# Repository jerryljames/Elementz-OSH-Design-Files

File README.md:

# Elementz Engineers Guild Pvt. Ltd. 

## Elementz-OSH-Design-Files
Open Source Hardware Design Files by Elementz

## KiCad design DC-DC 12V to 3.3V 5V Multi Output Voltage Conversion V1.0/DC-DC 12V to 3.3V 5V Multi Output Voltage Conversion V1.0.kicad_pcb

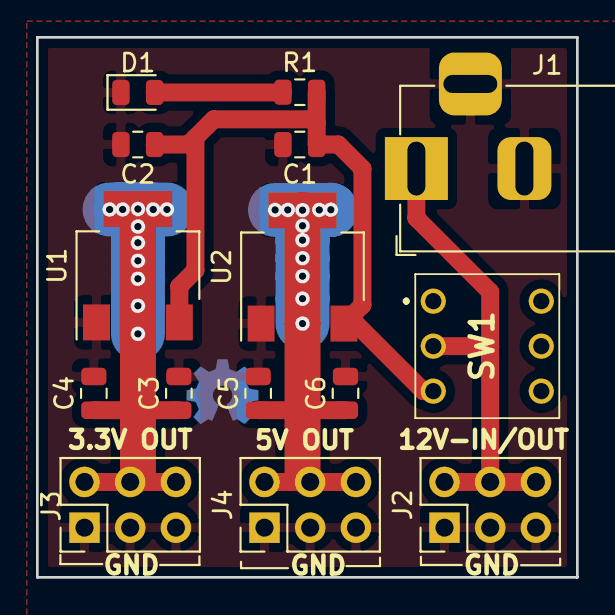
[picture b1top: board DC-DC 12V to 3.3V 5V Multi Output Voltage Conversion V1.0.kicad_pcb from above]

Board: 2 copper layers, 30.0 x 30.0 mm, 15 parts (0 on the bottom side), 6 nets.

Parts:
C1, C2, C3, C4, C5, C6: C; C_0805_2012Metric
D1: LED; LED_0805_2012Metric
J1: Barrel_Jack_Switch; BarrelJack_Horizontal
J2, J3, J4: Conn_02x03_Counter_Clockwise; PinHeader_2x03_P2.54mm_Vertical
R1: R; R_0805_2012Metric
SW1: SW_Push_DPDT; TL2285OA
U1: AMS1117-3.3; SOT-223-3_TabPin2
U2: AMS1117-5.0; SOT-223-3_TabPin2

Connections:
+3V3: C3.1, C4.1, J3.2, J3.4, J3.6, U1.2
+5V: C5.1, C6.1, J4.2, J4.4, J4.6, U2.2
+12V: J1.1, J2.2, J2.4, J2.6, SW1.2
GND: C1.2, C2.2, C3.2, C4.2, C5.2, C6.2, D1.1, J1.2, J1.3, J2.1, J2.3, J2.5, J3.1, J3.3, J3.5, J4.1, J4.3, J4.5, U1.1, U2.1
unnamed: D1.2, R1.1
VCC: C1.1, C2.1, R1.2, SW1.3, U1.3, U2.3

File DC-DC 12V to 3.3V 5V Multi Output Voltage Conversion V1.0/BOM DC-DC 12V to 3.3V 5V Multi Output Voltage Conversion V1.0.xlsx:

Comment | Designator | Footprint
10uF Unpolarized capacitor | C1,C2,C3,C5 | C_0805_2012Metric
0.1uF Unpolarized capacitor | C4,C6 | C_0805_2012Metric
LED Light emitting diode | D1 | LED_0805_2012Metric
Barrel_Jack_Switch DC Barrel Jack with an internal switch | J1 | BarrelJack_Horizontal
Conn_02x03_Counter_Clockwise | J2,J3,J4 | PinHeader_2x03_P2.54mm_Vertical
1K Resistor | R1 | R_0805_2012Metric
SW_Push_DPDT | SW1 | TL2285OA
AMS1117-3.3 1A Low Dropout regulator, positive, 3.3V fixed output, SOT-223 | U1 | SOT-223-3_TabPin2
AMS1117-5.0 1A Low Dropout regulator, positive, 5.0V fixed output, SOT-223 | U2 | SOT-223-3_TabPin2

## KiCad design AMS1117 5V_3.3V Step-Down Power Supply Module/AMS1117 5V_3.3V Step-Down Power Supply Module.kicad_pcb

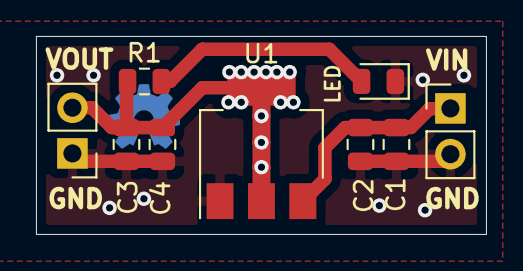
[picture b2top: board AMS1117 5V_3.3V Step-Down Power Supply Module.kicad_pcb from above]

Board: 2 copper layers, 25.0 x 11.0 mm, 9 parts (0 on the bottom side), 4 nets.

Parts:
C1, C2, C3, C4: C; C_0805_2012Metric
D1: LED; LED_0805_2012Metric
J1: Conn_01x02_Male; PinHeader_1x02_P2.54mm_Vertical
Je: Conn_01x02_Male; PinHeader_1x02_P2.54mm_Vertical
R1: R; R_0805_2012Metric
U1: AMS1117-3.3; SOT-223-3_TabPin2

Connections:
GND: C1.2, C2.2, C3.2, C4.2, D1.1, J1.2, Je.1, U1.1
unnamed: C1.1, C2.1, J1.1, U1.3
unnamed: C3.1, C4.1, Je.2, R1.2, U1.2
unnamed: D1.2, R1.1

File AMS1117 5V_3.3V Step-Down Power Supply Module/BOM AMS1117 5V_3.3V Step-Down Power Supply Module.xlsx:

Comment | Designator | Footprint
10uF Unpolarized capacitor | C1,C3 | C_0805_2012Metric
0.1uF Unpolarized capacitor | C2,C4 | C_0805_2012Metric
LED Light emitting diode | D1 | LED_0805_2012Metric
DNP (Do Not Populate) | J1,J2 | PinHeader_1x02_P2.54mm_Vertical
1K Resistor | R1 | R_0805_2012Metric
AMS1117 1A Low Dropout regulator, positive, fixed output, SOT-223 – 5V or 3.3V 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 | U1 | SOT-223-3_TabPin2

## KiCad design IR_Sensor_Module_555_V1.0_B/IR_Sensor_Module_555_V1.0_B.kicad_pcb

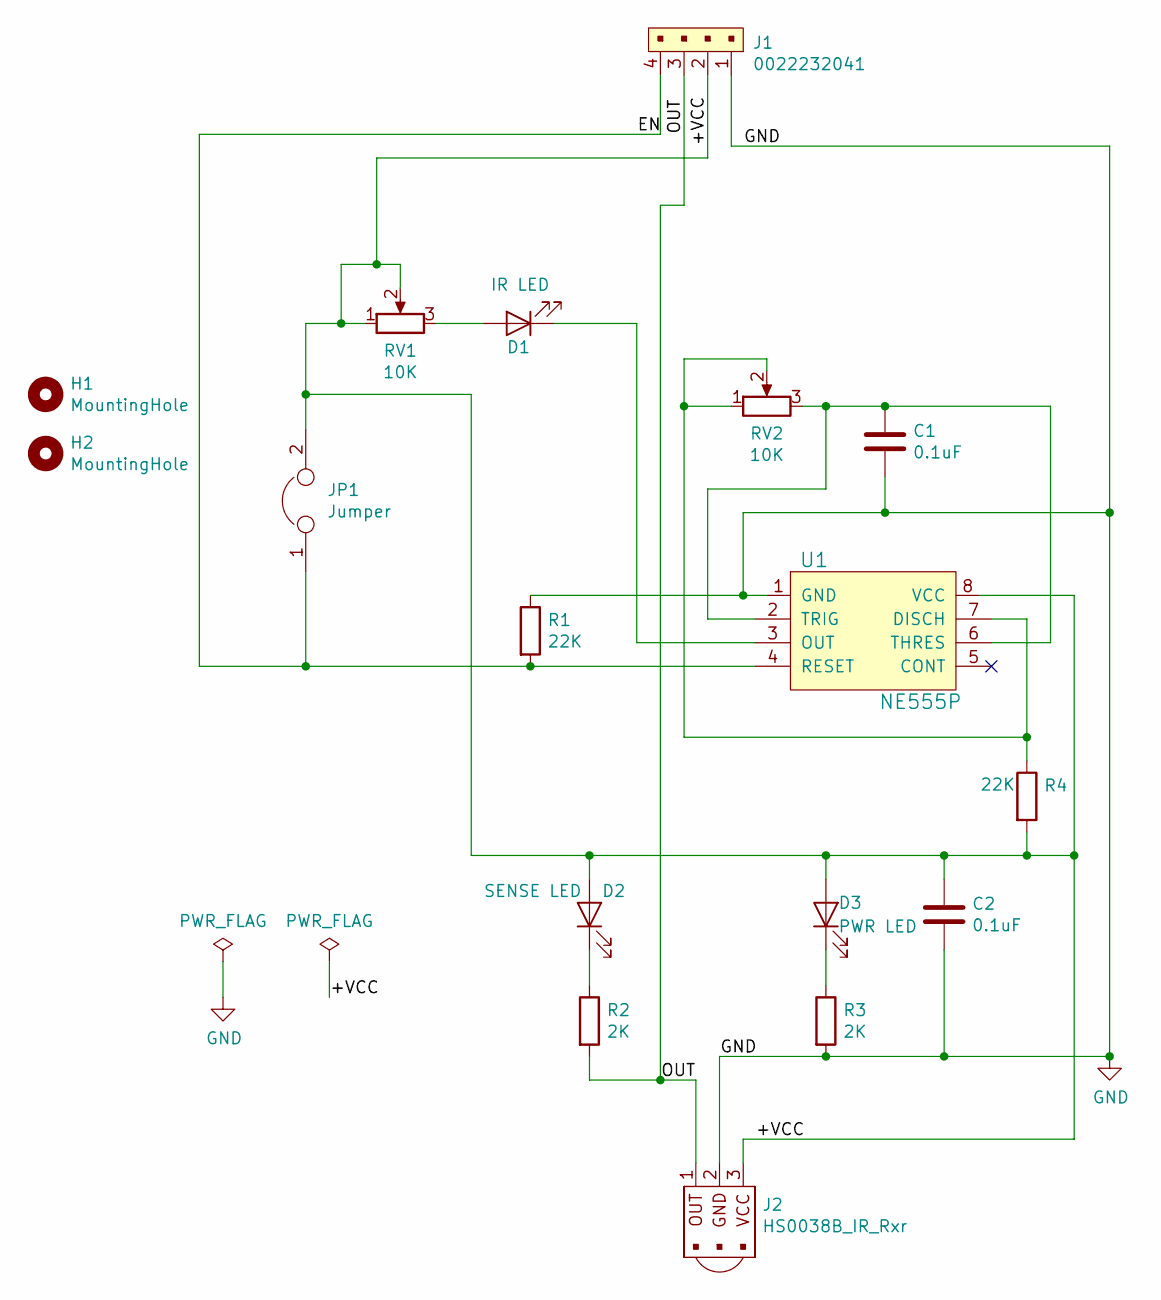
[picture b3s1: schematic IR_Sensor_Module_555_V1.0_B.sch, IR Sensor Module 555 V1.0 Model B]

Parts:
C1, C2: 0.1uF; C_Disc_D5.0mm_W2.5mm_P2.50mm
D1: IR LED; LED_D5.0mm
D2: SENSE LED; LED_D3.0mm
D3: PWR LED; LED_D3.0mm
H1, H2: MountingHole; MountingHole_3mm
J1: 0022232041; PinHeader_1x04_P2.54mm_Vertical; MPN 0022232041; Digi-Key_PN WM4202-ND
J2: HS0038B_IR_Rxr; PinHeader_1x3_P2.54_Drill1.1mm; MPN 640456-3; Digi-Key_PN A19470-ND
JP1: Jumper; PinHeader_1x02_P2.54mm_Vertical
R1, R4: 22K; R_Axial_DIN0204_L3.6mm_D1.6mm_P7.62mm_Horizontal
R2, R3: 2K; R_Axial_DIN0204_L3.6mm_D1.6mm_P7.62mm_Horizontal
RV1, RV2: 10K; Potentiometer_Bourns_3339P_Vertical_HandSoldering
U1: NE555P; DIP-8_W7.62mm; MPN NE555P; Digi-Key_PN 296-1411-5-ND

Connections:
/+VCC: C2.1, D2.2 (A), D3.2 (A), J1.2, J2.3, JP1.2, R4.2, RV1.1, RV1.2, U1.8 (VCC)
/EN: J1.4, JP1.1, R1.2, U1.4 (RESET)
/OUT: J1.3, J2.1, R2.2
GND: C1.2, C2.2, J1.1, J2.2, R1.1, R3.2, U1.1 (GND)
unnamed: C1.1, RV2.3, U1.2 (TRIG), U1.6 (THRES)
unnamed: D1.1 (K), U1.3 (OUT)
unnamed: D1.2 (A), RV1.3
unnamed: D2.1 (K), R2.1
unnamed: D3.1 (K), R3.1
unnamed: R4.1, RV2.1, RV2.2, U1.7 (DISCH)

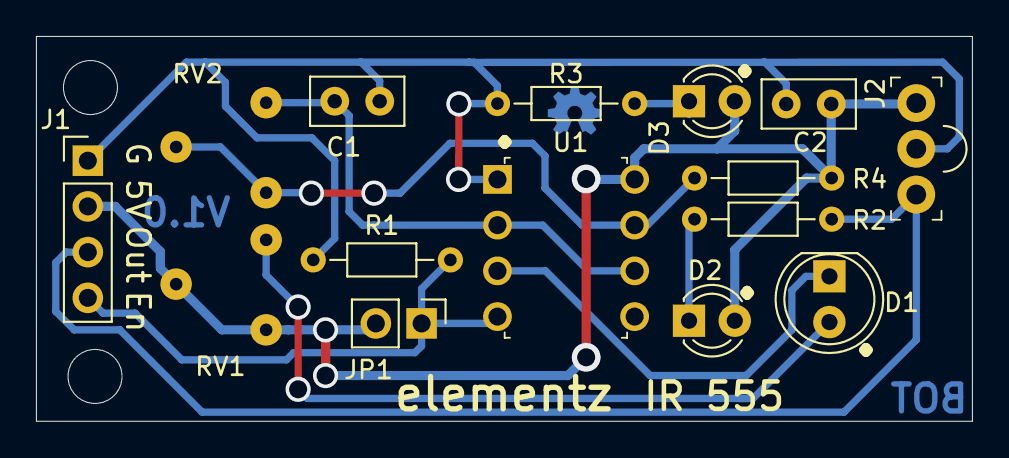
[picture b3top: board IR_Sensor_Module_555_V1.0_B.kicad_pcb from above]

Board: 2 copper layers, 52.0 x 21.4 mm, 17 parts (0 on the bottom side), 10 nets.

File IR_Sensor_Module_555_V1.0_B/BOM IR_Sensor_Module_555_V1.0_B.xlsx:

Comment | Designator | Footprint
0.001uF Unpolarized capacitor | C1 | C_Disc_D5.0mm_W2.5mm_P2.50mm
0.1uF Unpolarized capacitor | C2 | C_Disc_D5.0mm_W2.5mm_P2.50mm
IR LED Light emitting diode | D1 | LED_D5.0mm
Green LED | D2 | LED_D3.0mm
Red LED | D3 | LED_D3.0mm
Pin Header | J1 | PinHeader_1x04_P2.54mm_Horizontal(90 degree)
HS0038B | J2 | HS0038B 3 Pin
Jumper Jumper, normally closed | JP1 | PinHeader_1x02_P2.54mm_Vertical
22K Resistor | R1,R4 | R_Axial_DIN0204_L3.6mm_D1.6mm_P7.62mm_Horizontal
2K Resistor | R2,R3 | R_Axial_DIN0204_L3.6mm_D1.6mm_P7.62mm_Horizontal
10K Potentiometer | RV1,RV2 | Potentiometer_Bourns_3339P_Vertical_HandSoldering
NE555P | U1 | DIP-8_W7.62mm

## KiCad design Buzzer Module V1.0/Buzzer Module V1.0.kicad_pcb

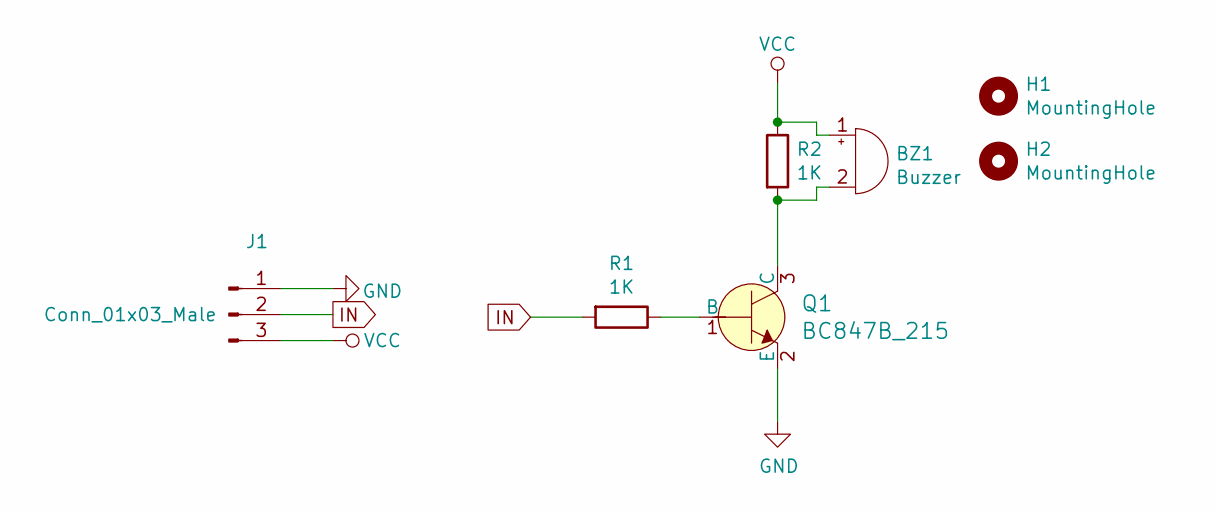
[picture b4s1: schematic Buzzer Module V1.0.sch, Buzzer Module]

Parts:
BZ1: Buzzer; Buzzer_12x9.5RM7.6
H1, H2: MountingHole; MountingHole_3mm
J1: Conn_01x03_Male; PinHeader_1x03_P2.54mm_Vertical
Q1: BC847B_215; SOT-23-3; MPN BC847B,215; Digi-Key_PN 1727-2921-1-ND
R1, R2: 1K; R_0805_2012Metric

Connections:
/IN: J1.2, R1.2
GND: J1.1, Q1.2 (E)
unnamed: BZ1.2 (+), Q1.3 (C), R2.2
unnamed: Q1.1 (B), R1.1
VCC: BZ1.1 (-), J1.3, R2.1

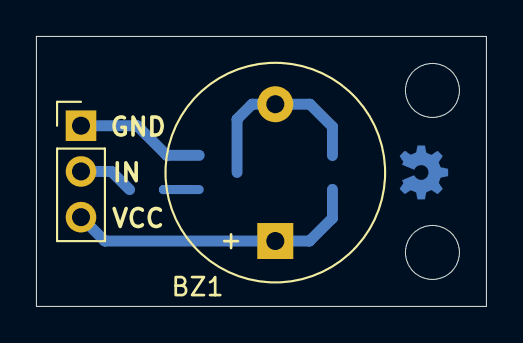
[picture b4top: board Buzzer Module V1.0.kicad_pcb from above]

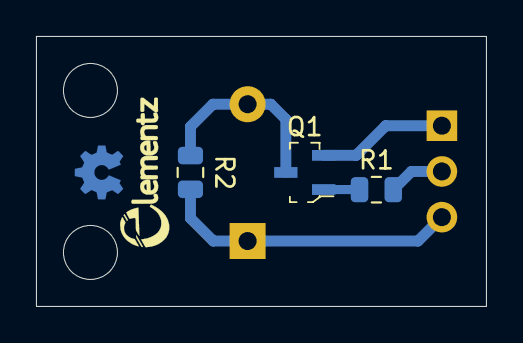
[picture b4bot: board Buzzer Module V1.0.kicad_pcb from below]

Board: 2 copper layers, 25.0 x 15.0 mm, 7 parts (3 on the bottom side), 5 nets.

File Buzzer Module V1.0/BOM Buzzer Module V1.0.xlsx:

Comment | Designator | Footprint
Buzzer Buzzer, polarized | BZ1 | Buzzer_12x9.5RM7.6
Conn_01x03_Male Generic connector, single row, 01x03, Horizontal | J1 | PinHeader_1x03_P2.54mm_Horizontal
BC847 | Q1 | SOT-23-3
1K Resistor | R1,R2 | R_0805_2012Metric

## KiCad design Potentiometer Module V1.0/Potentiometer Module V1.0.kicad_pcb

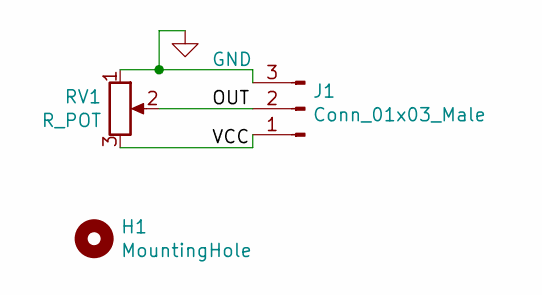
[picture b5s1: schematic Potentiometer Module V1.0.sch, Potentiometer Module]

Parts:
H1: MountingHole; MountingHole_3mm
J1: Conn_01x03_Male; PinHeader_1x03_P2.54mm_Vertical
RV1: R_POT; Potentiometer_Alps_RK163_Single_Horizontal

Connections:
/OUT: J1.2, RV1.2
/VCC: J1.1, RV1.3
GND: J1.3, RV1.1

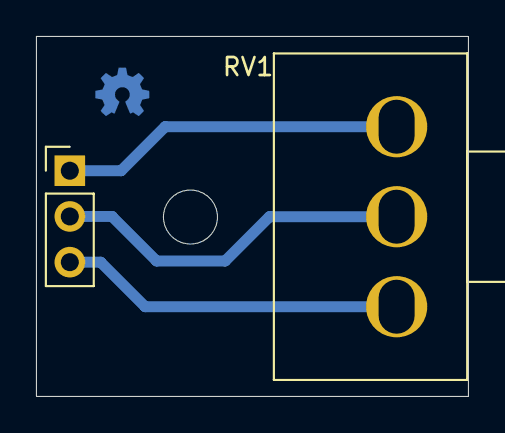
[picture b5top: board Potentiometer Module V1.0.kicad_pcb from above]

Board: 2 copper layers, 24.0 x 20.0 mm, 3 parts (0 on the bottom side), 3 nets.

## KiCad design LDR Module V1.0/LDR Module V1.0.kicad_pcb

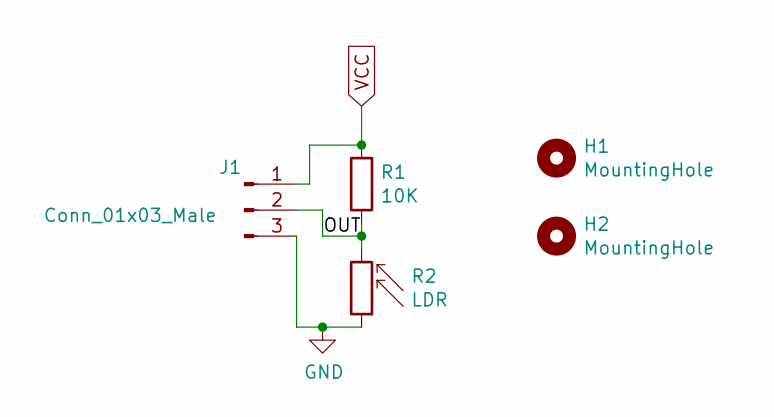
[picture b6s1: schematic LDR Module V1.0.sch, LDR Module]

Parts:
H1, H2: MountingHole; MountingHole_3mm
J1: Conn_01x03_Male; PinHeader_1x03_P2.54mm_Vertical
R1: 10K; R_0805_2012Metric
R2: LDR; R_LDR_5.0x4.1mm_P3mm_Vertical

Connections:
/OUT: J1.2, R1.1, R2.2
GND: J1.3, R2.1
VCC: J1.1, R1.2

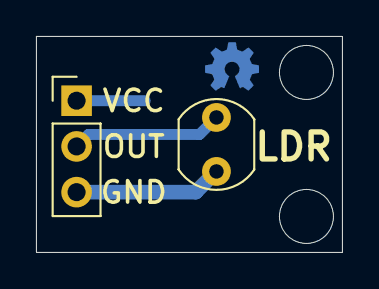
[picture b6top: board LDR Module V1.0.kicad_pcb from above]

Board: 2 copper layers, 17.0 x 12.0 mm, 5 parts (1 on the bottom side), 3 nets.

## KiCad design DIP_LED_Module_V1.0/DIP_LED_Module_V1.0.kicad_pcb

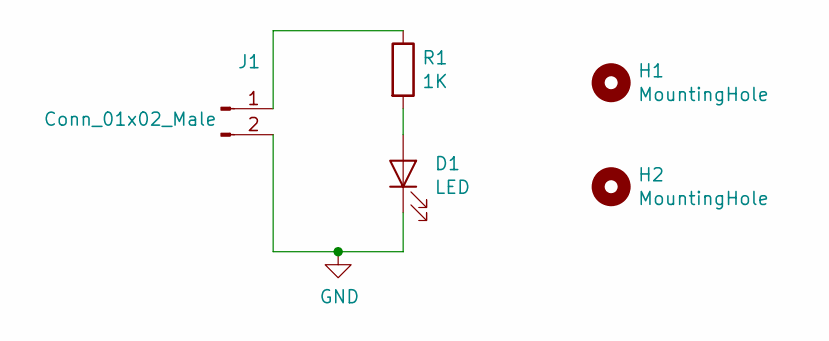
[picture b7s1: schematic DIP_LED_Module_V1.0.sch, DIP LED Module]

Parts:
D1: LED; LED_D5.0mm
H1, H2: MountingHole; MountingHole_3mm
J1: Conn_01x02_Male; PinHeader_1x02_P2.54mm_Vertical
R1: 1K; R_0805_2012Metric

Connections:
GND: D1.1 (K), J1.2
unnamed: D1.2 (A), R1.2
unnamed: J1.1, R1.1

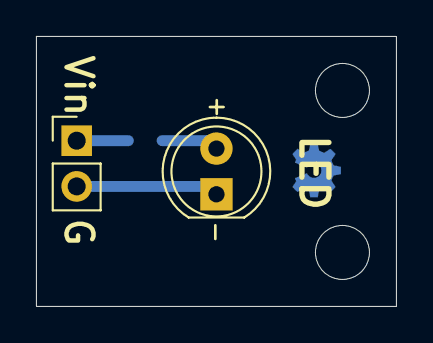
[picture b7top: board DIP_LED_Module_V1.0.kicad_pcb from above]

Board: 2 copper layers, 20.0 x 15.0 mm, 5 parts (1 on the bottom side), 3 nets.

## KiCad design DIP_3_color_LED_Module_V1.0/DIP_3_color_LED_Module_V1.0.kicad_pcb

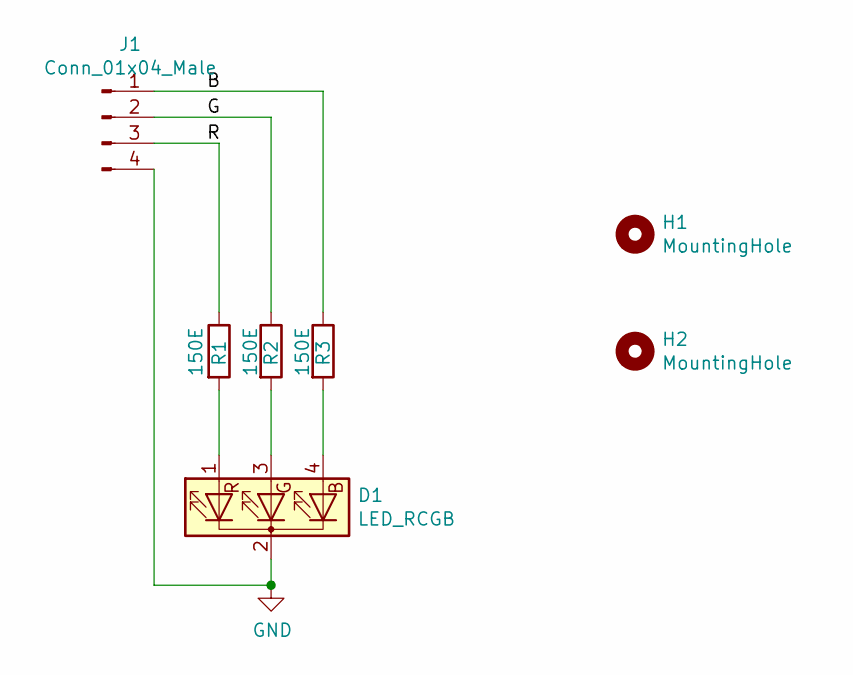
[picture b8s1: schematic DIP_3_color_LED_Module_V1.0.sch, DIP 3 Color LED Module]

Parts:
D1: LED_RCGB; LED_D5.0mm-4_RGB
H1, H2: MountingHole; MountingHole_3mm
J1: Conn_01x04_Male; PinHeader_1x04_P2.54mm_Vertical
R1, R2, R3: 150E; R_0805_2012Metric

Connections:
/B: J1.1, R3.1
/G: J1.2, R2.1
/R: J1.3, R1.1
GND: D1.2 (K), J1.4
unnamed: D1.1 (RA), R1.2
unnamed: D1.3 (GA), R2.2
unnamed: D1.4 (BA), R3.2

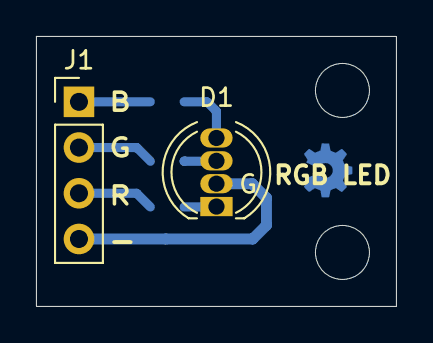
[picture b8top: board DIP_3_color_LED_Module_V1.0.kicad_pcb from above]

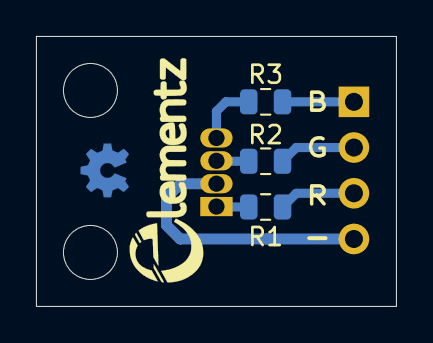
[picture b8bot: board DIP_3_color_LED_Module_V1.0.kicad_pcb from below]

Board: 2 copper layers, 20.0 x 15.0 mm, 7 parts (3 on the bottom side), 7 nets.

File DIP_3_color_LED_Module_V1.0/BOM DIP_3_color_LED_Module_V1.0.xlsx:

Comment | Designator | Footprint | Qty
RGB LED, Common Cathode | D1 | LED_D5.0mm-4_RGB | 1
Conn_01x04_Male Generic connector, single row, 01x04, Right angle | J1 | PinHeader_1x04_P2.54mm_Horizontal | 1
150E Resistor | R1,R2,R3 | R_0805_2012Metric | 3

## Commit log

2020-10-02 IR Sensor Module 555 V1.0
2020-10-02 L298N Motor Driver V1.0
2020-10-02 MLX90614 IR V1.0
2020-10-02 IRF520 MOSFET Driver V1.0
2020-10-02 MQxx Gas Sensor V1.0
2020-10-02 IR Sensor Module V1.0
2020-10-09 3 Color(RGB)LED Module V1.0 added
2020-11-24 Added DIP 3 Color LED Module Schematic in pdf
2020-11-24 DIP LED Module V1.0
2020-11-24 LDR Module V1.0
2020-11-24 Potentiometer Module V1.0
2020-11-24 Buzzer Module V1.0
2020-11-24 IR_Sensor_Module_555_V1.1
    Trace width & via diameter increased
2020-11-24 IR_Sensor_Module_555_V1.0_B
    Single Layer version of IR 555 with Through hole components
2020-11-24 AMS1117 5V/3.3V Step-Down Power Supply Module
2020-11-24 DC-DC 12V to 3.3V 5V Multi Output Voltage Conversion V1.0
